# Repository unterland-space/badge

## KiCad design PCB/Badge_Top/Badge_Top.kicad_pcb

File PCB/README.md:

# Unterland Badge
The Unterland Badge is made of two PCBs, Top and Bottom.

## External Parts
- Lithium Polymer Battery with JST PH 2 Connector and Built-In Protection Circuit
  - The max. dimensions are 50mm length x 30mm width x 4mm height
  - The JST PH 2 Connector has pin 1 as positive terminal
  - This Badge does not have any protection against under- or overvoltage. Please make sure the battery has a protection circuit built-in.

- Screws
  - 3x Metal M2 5-7mm
  - 3x Nylon M2 5-7mm

## Badge Top

The Top PCB is made with ENIG finish and has 14 SK6806 RGB LEDs. It is connected to the bottom pcb via 3 of the standoffs.

## Badge Bottom

The Bottom PCB is made with HASL lead-free and has the brains of the badge.
Features:
- WCH CH32V305 Microcontroller
- TI PCM5100 DAC
- 2x USB-C (1x USB High-Speed, 1x USB Full-Speed)
- 2x 3.5mm TRS Audio Jack, for Data and Audio communication with the Fl0wer or other Badges / Equipment
- 2x Rotating Buttons for UI
- TP4054 LiPo charge controller
- Optional Micro SD-Card with SDIO
- Optional GPIOs as 2.54mm Pinheader

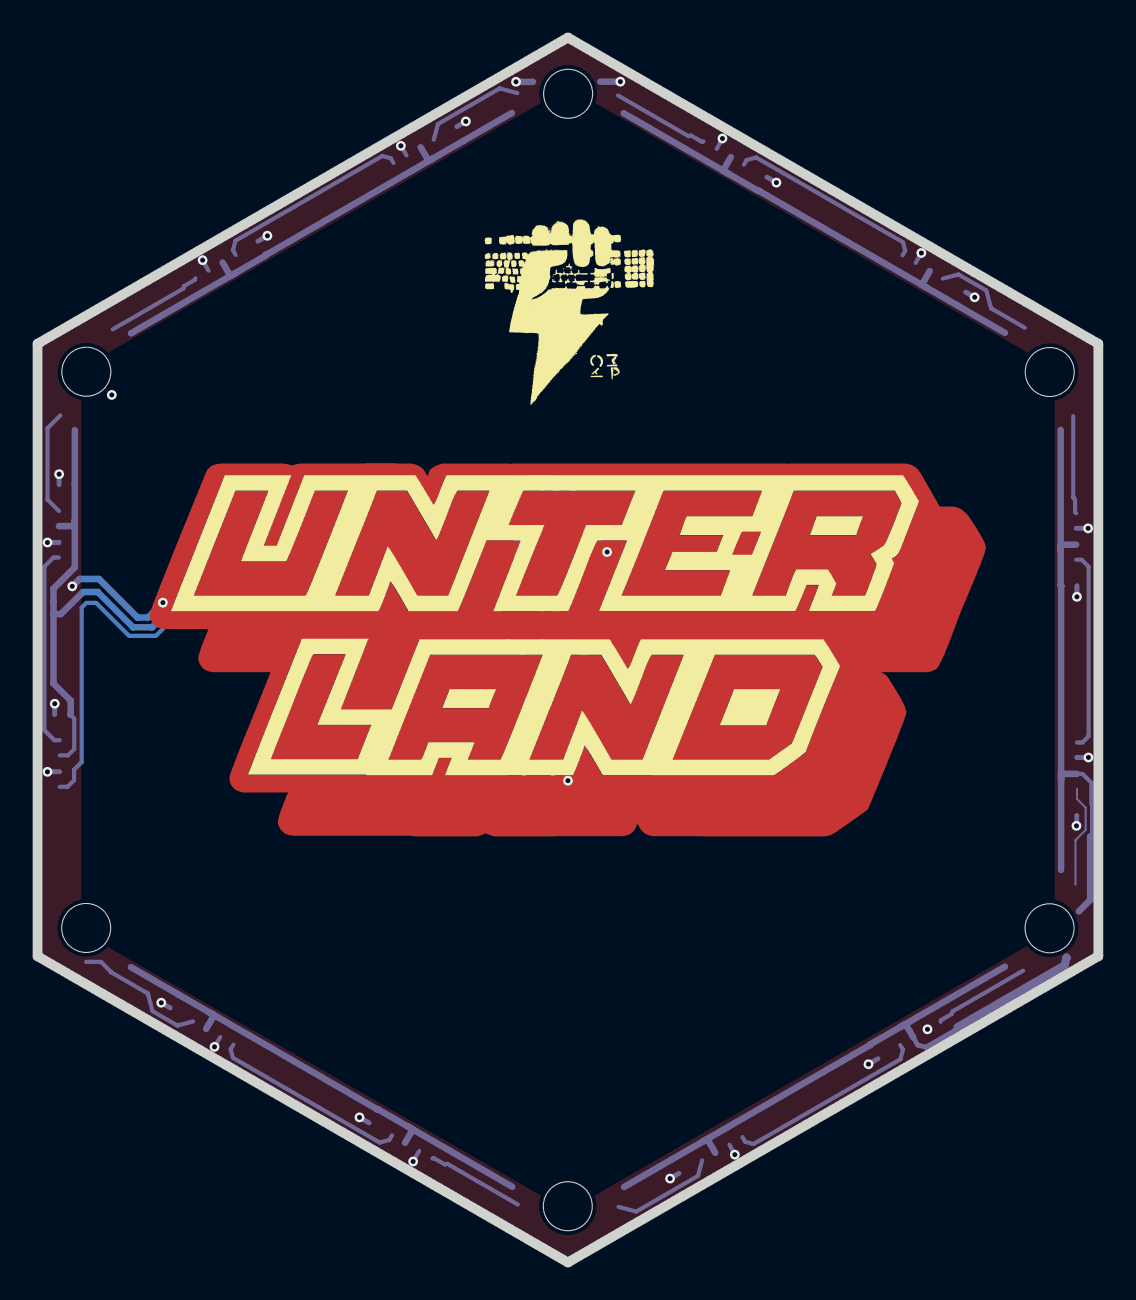
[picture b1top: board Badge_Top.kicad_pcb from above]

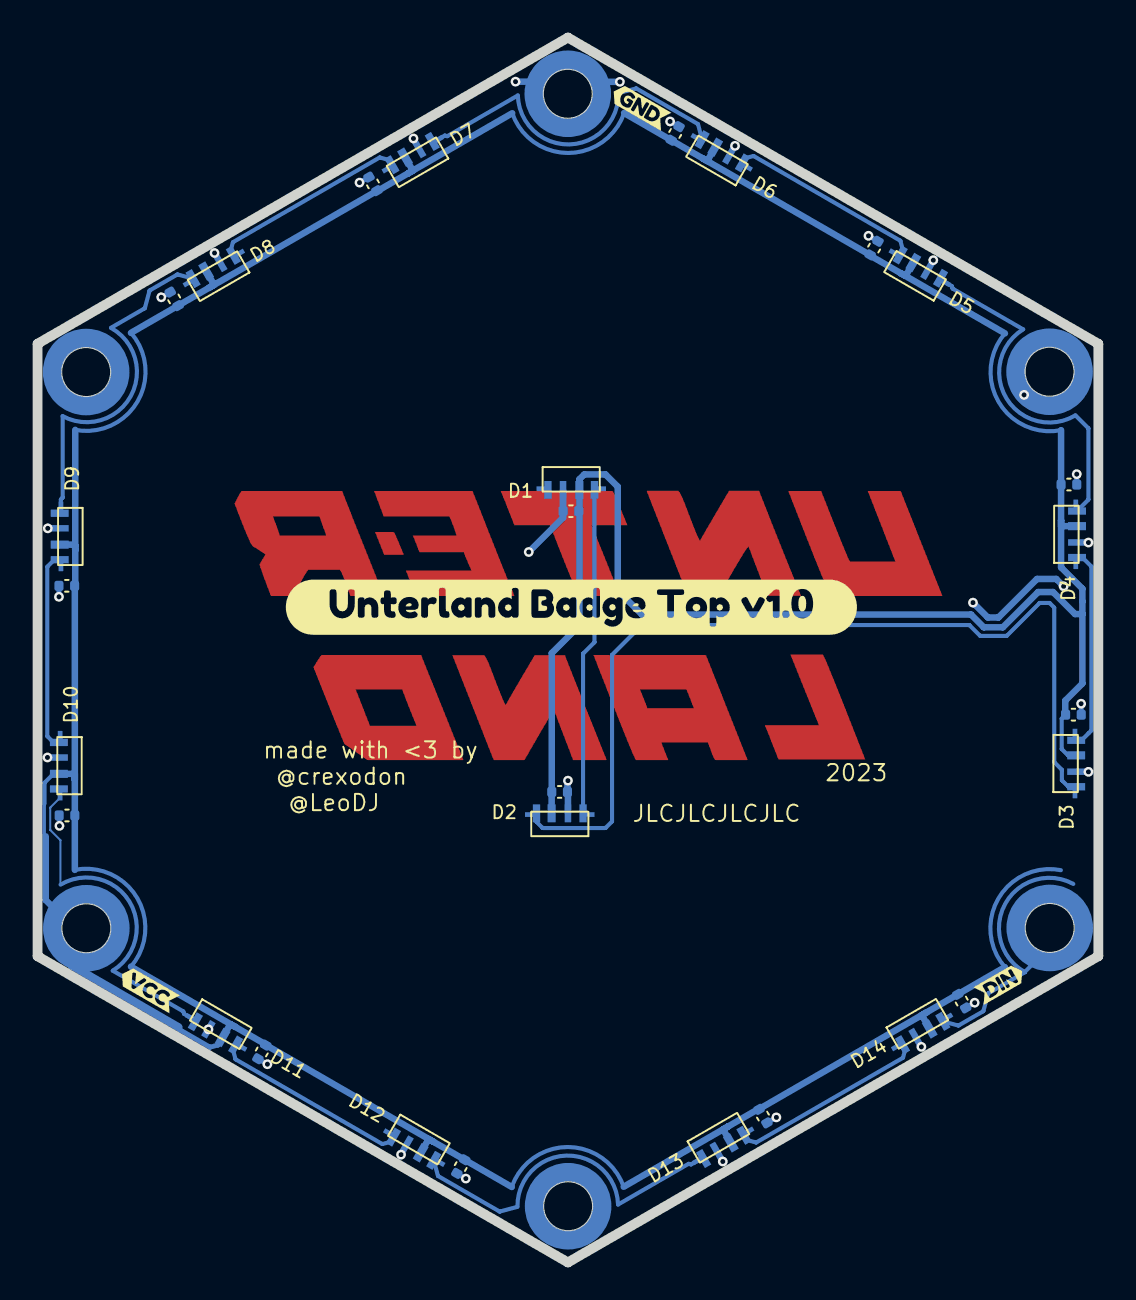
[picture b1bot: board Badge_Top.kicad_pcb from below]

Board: 2 copper layers, 65.0 x 75.0 mm, 48 parts (38 on the bottom side), 16 nets.

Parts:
1, 2, 3, 4, 5: 9966cd8a-fa79-43c1-83f9-02636052551b
6, 7, 8, 9, 10: 2488e693-1bf8-4f98-9257-4c9c6a257d6e
C1, C2, C3, C4, C5, C6, C7, C8, C9, C10, C11, C12, C13, C14: 100n; C_0402_1005Metric
D1, D2, D3, D4, D5, D6, D7, D8, D9, D10, D11, D12, D13, D14: SK6805; SK6805SIDE-G-001
J1, J2, J3, J4, J5, J6: Conn_01x01; Mounting_Wuerth_WA-SMSI-M2_H7mm_9774070243
kibuzzard-64BC5FAA: G***; kibuzzard-64BC5FAA
kibuzzard-64BC6378: G***; kibuzzard-64BC6378
kibuzzard-64BC6382: G***; kibuzzard-64BC6382
kibuzzard-64BC6413: G***; kibuzzard-64BC6413

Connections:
DIN: D14.3 (DIN), J3.1
GND: C1.2, C2.2, C3.2, C4.2, C5.2, C6.2, C7.2, C8.2, C9.2, C10.2, C11.2, C12.2, C13.2, C14.2, D1.2 (VSS), D2.2 (VSS), D3.2 (VSS), D4.2 (VSS), D5.2 (VSS), D6.2 (VSS), D7.2 (VSS), D8.2 (VSS), D9.2 (VSS), D10.2 (VSS), D11.2 (VSS), D12.2 (VSS), D13.2 (VSS), D14.2 (VSS), J1.1
unnamed: D1.3 (DIN), D2.1 (DOUT)
unnamed: D2.3 (DIN), D3.1 (DOUT)
unnamed: D3.3 (DIN), D4.1 (DOUT)
unnamed: 5.1, D4.3 (DIN), D5.1 (DOUT)
unnamed: D5.3 (DIN), D6.1 (DOUT)
unnamed: 4.1, D6.3 (DIN), D7.1 (DOUT)
unnamed: D7.3 (DIN), D8.1 (DOUT)
unnamed: 3.1, D8.3 (DIN), D9.1 (DOUT)
unnamed: 2.1, D10.3 (DIN), D11.1 (DOUT)
unnamed: D9.3 (DIN), D10.1 (DOUT)
unnamed: D11.3 (DIN), D12.1 (DOUT)
unnamed: 1.1, D12.3 (DIN), D13.1 (DOUT)
unnamed: D13.3 (DIN), D14.1 (DOUT)
VDD: 6.1, 7.1, 8.1, 9.1, 10.1, C1.1, C2.1, C3.1, C4.1, C5.1, C6.1, C7.1, C8.1, C9.1, C10.1, C11.1, C12.1, C13.1, C14.1, D1.4 (VDD), D2.4 (VDD), D3.4 (VDD), D4.4 (VDD), D5.4 (VDD), D6.4 (VDD), D7.4 (VDD), D8.4 (VDD), D9.4 (VDD), D10.4 (VDD), D11.4 (VDD), D12.4 (VDD), D13.4 (VDD), D14.4 (VDD), J5.1

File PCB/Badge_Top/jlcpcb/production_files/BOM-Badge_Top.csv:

Comment,Designator,Footprint,LCSC
100n,"C1,C10,C11,C12,C13,C14,C2,C3,C4,C5,C6,C7,C8,C9",C_0402_1005Metric,C1525
SK6805,"D1,D10,D11,D12,D13,D14,D2,D3,D4,D5,D6,D7,D8,D9",SK6805SIDE-G-001,C2909060
Conn_01x01,"J1,J2,J3,J4,J5,J6",Mounting_Wuerth_WA-SMSI-M2_H7mm_9774070243,C2916355

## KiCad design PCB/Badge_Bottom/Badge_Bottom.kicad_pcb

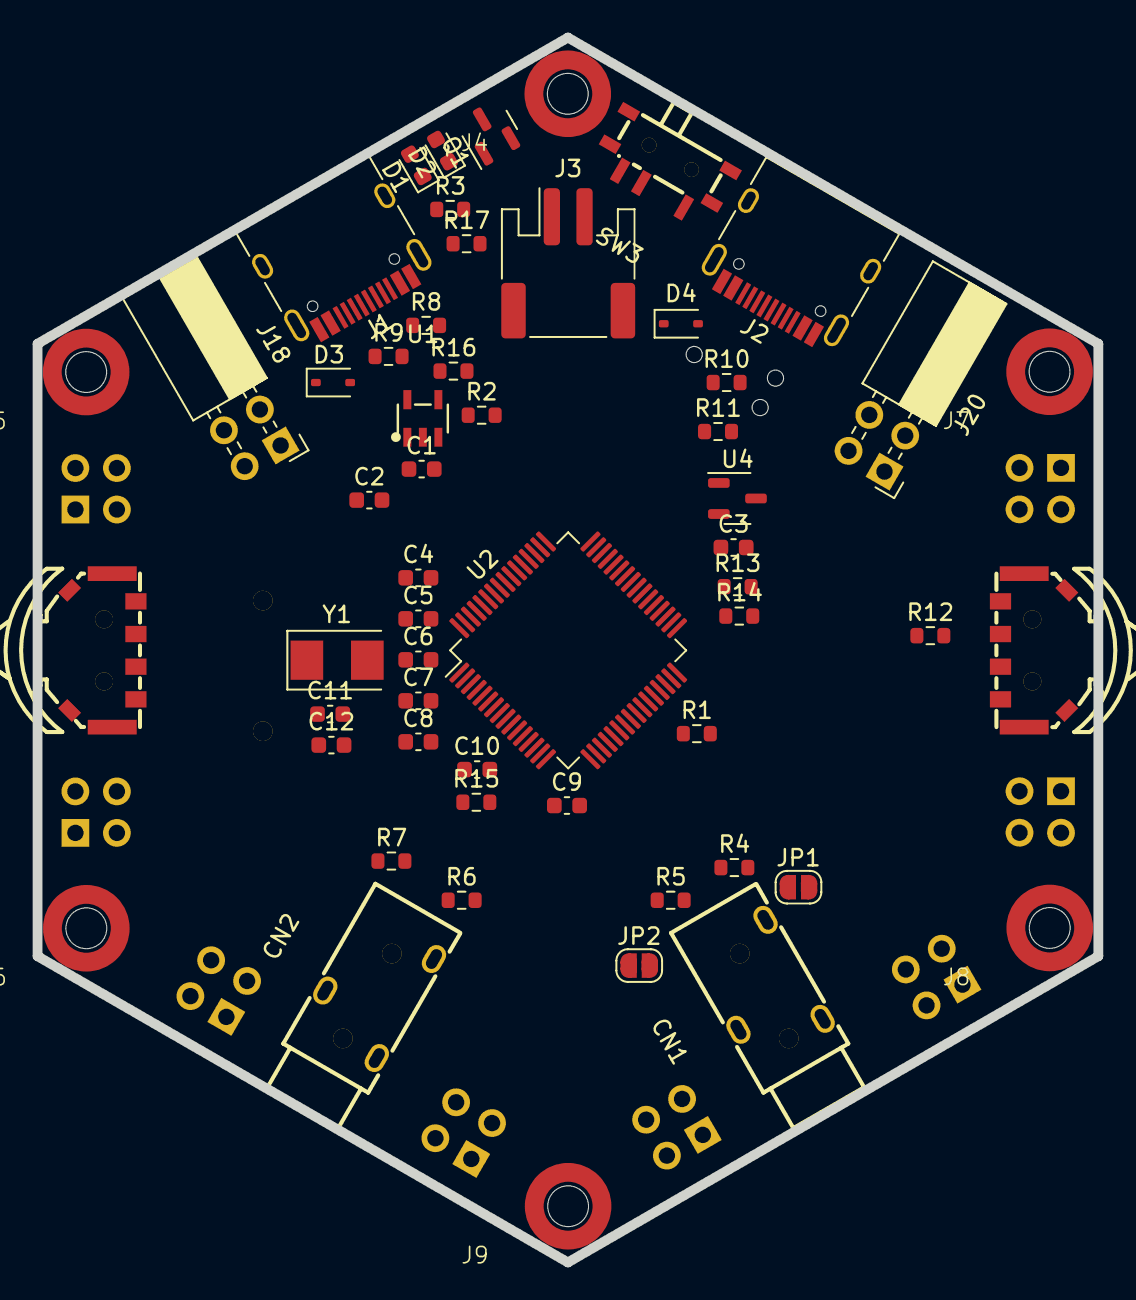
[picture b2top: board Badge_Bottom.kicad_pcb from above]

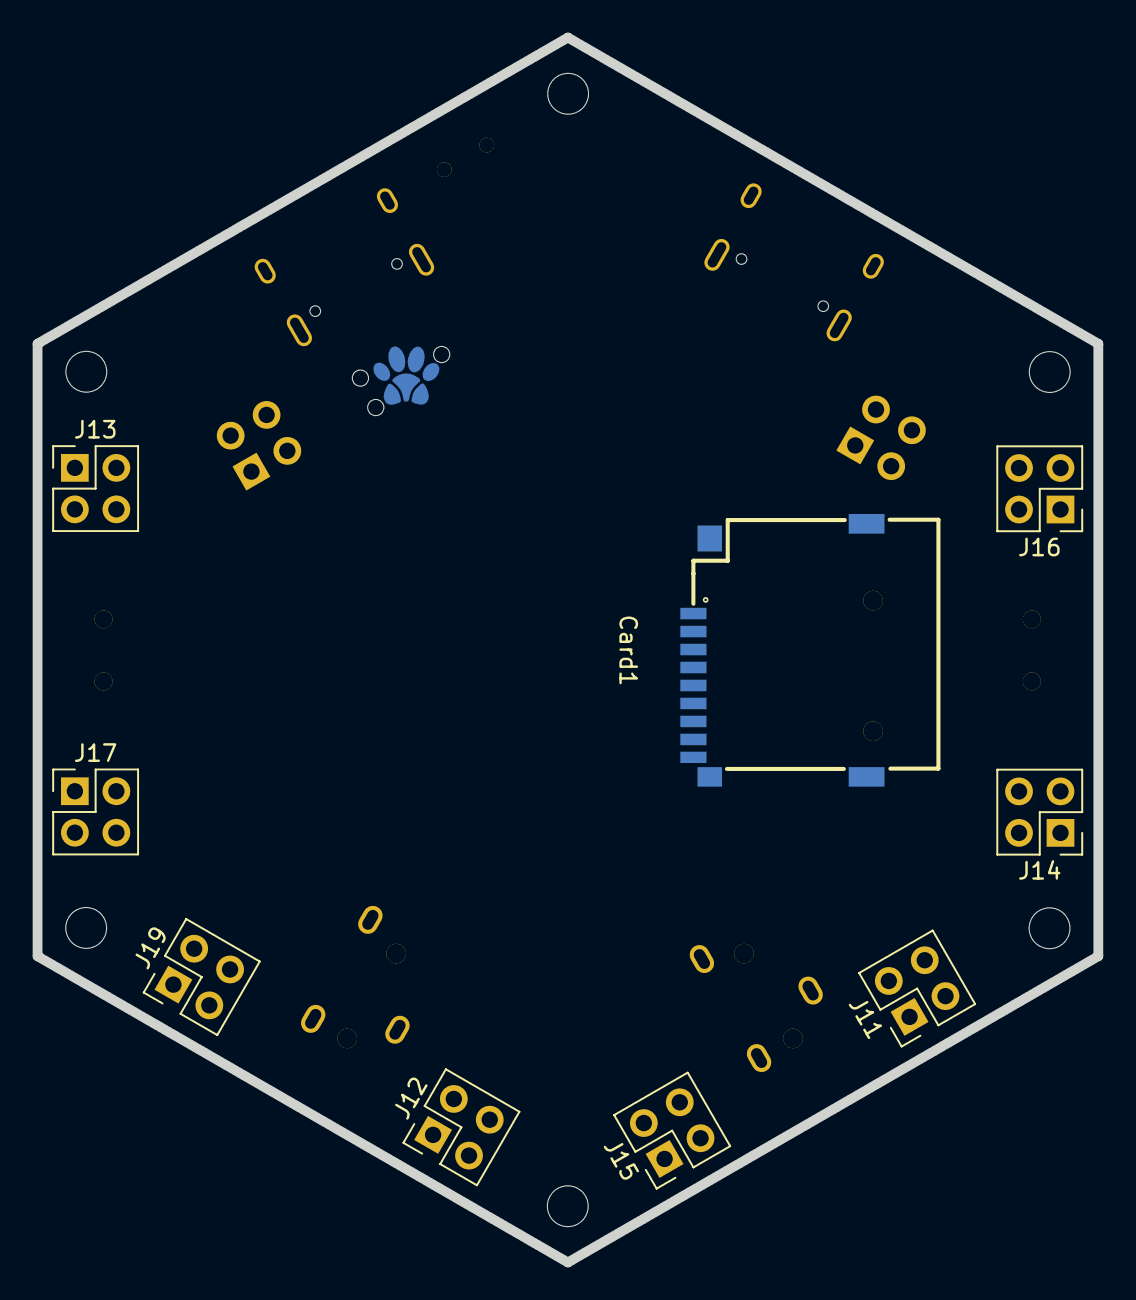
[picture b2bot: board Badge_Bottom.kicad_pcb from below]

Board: 2 copper layers, 65.0 x 75.0 mm, 66 parts (10 on the bottom side), 70 nets, no tracks yet.

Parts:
C1, C2, C3: 1u; C_0603_1608Metric
C4, C5, C6, C7, C8, C9, C10: 0.1u; C_0603_1608Metric
C11, C12: 20p; C_0603_1608Metric
CN1: JACK_IN; AUDIO-TH_HOOYA_PJ-320
CN2: JACK_OUT; AUDIO-TH_HOOYA_PJ-320
Card1: MicroSD; TF-SMD_TF-PUSH
D1: CHG; LED_0603_1608Metric
D2: USER; LED_0603_1608Metric
D3, D4: 1N5819; D_SOD-323
J1: USB_FS; USB_C_Receptacle_HRO_TYPE-C-31-M-12
J2: USB_HS; USB_C_Receptacle_HRO_TYPE-C-31-M-12
J3: BAT; JST_PH_S2B-PH-SM4-TB_1x02-1MP_P2.00mm_Horizontal
J4, J6, J8: Nylon Screw; Standoff_Pad_M2
J5, J7, J9: Metal Screw; Standoff_Pad_M2
J10: Debug; Paw-Connect_RevB_TC2030-IDC-NL_2x03_P1.27mm_Vertical
J11, J19: Power; PinHeader_2x02_P2.54mm_Vertical
J12, J13, J14, J15, J16, J17: GPIO; PinHeader_2x02_P2.54mm_Vertical
J18: SAO; PinSocket_2x02_P2.54mm_Horizontal
J20: Debug; PinSocket_2x02_P2.54mm_Horizontal
JP1, JP2: SolderJumper_2_Open; SolderJumper-2_P1.3mm_Open_RoundedPad1.0x1.5mm
Q1: AO3400A; SOT-23
R1, R12, R15, R16: 10k; R_0603_1608Metric
R2: 1.65k; R_0603_1608Metric
R3: 330; R_0603_1608Metric
R4, R5, R6, R7: 100; R_0603_1608Metric
R8, R9, R10, R11: 5k1; R_0603_1608Metric
R13, R14: 1M; R_0603_1608Metric
R17: 1k; R_0603_1608Metric
SW1, SW2: TM-2024A; SW-SMD_TM-2024A
SW3: MSK12C02-HB; SW-TH_MSK12C02-HB-1
U1: TP4054; SOT-23-5_L3.0-W1.7-P0.95-LS2.8-BL
U2: CH32V305RBT6; LQFP-64_10x10mm_P0.5mm
U4: XC6206PxxxMR; SOT-23-3
Y1: 8M; Crystal_SMD_5032-2Pin_5.0x3.2mm

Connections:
+3V3: C2.2, C4.1, C5.1, C6.2, C7.1, C8.1, Card1.4 (VDD), J10.1, J11.1, J11.2, J18.1, J19.1, R15.2, R16.1, R17.2, SW1.4, SW2.4, U2.13 (VDDA), U2.19 (VDD), U2.32 (VIO), U2.48 (VDD), U2.64 (VIO), U4.2 (VO)
+BATT: J3.1, SW3.1, U1.3 (BAT)
BOOT0: R12.2, SW1.3, U2.29 (PB10), U2.60 (BOOT0)
GND: C1.1, C2.1, C3.1, C4.2, C5.2, C6.1, C7.2, C8.2, C9.2, C10.1, C11.1, C12.1, CN1.3, CN2.3, Card1.6 (VSS), Card1.10, Card1.11, Card1.12, Card1.13, J1.A1 (GND), J1.A12 (GND), J1.B1 (GND), J1.B12 (GND), J1.S1 (SHIELD), J2.A1 (GND), J2.A12 (GND), J2.B1 (GND), J2.B12 (GND), J2.S1 (SHIELD), J3.2, J10.5, J11.3, J11.4, J18.3, J19.3, J19.4, J20.1, Q1.2 (S), R1.2, R2.2, R8.2, R9.2, R10.2, R11.2, R12.1, R14.1, SW3.4, U1.2 (GND), U2.12 (VSSA), U2.18 (VSS), U2.31 (VSS), U2.47 (VSS), U2.63 (VSS), U4.1 (GND)
NRST: C10.2, J10.3, J20.3, R15.1, U2.7 (NRST)
unnamed: CN1.2, R5.2
unnamed: CN1.4, R4.2
unnamed: CN2.2, R7.2
unnamed: CN2.4, R6.2
unnamed: D1.1 (K), R3.1
unnamed: D2.2 (A), U2.23 (PA7)
unnamed: D2.1 (K), R17.1
unnamed: D3.2 (A), J1.A4 (VBUS), J1.A9 (VBUS), J1.B4 (VBUS), J1.B9 (VBUS)
unnamed: D4.2 (A), J2.A4 (VBUS), J2.A9 (VBUS), J2.B4 (VBUS), J2.B9 (VBUS)
unnamed: J1.A5 (CC1), R8.1
unnamed: J1.B5 (CC2), R9.1
unnamed: J2.A5 (CC1), R10.1
unnamed: J2.B5 (CC2), R11.1
unnamed: J4.1, Q1.3 (D)
unnamed: R3.2, U1.1 (CHRG)
unnamed: R2.1, U1.5 (PROG)
unnamed: R1.1, U2.28 (BOOT1/PB2)
unnamed: C11.2, U2.5 (OSC_IN), Y1.2
unnamed: C12.2, U2.6 (OSC_OUT), Y1.1
PA0-GPIO: J17.1, U2.14 (WAKEUP/PA0)
PA1-ADC_IN1: C9.1, R13.1, R14.2, U2.15 (PA1)
PA2-ADC_IN2/USART2_TX: JP2.2 (B), R5.1, U2.16 (PA2)
PA3-ADC_IN_3/USART2_RX: JP1.2 (B), R4.1, U2.17 (PA3)
PA4-DAC1: R6.1, U2.20 (PA4), U2.42 (PA9)
PA6-LEDFET: Q1.1 (G), R16.2, U2.22 (PA6)
PA8-TIM1: J6.1, U2.41 (PA8)
PA10-USART1_RX: R7.1, U2.21 (PA5), U2.43 (PA10)
PA11-USBFS_DM: J1.A7 (D-), J1.B7 (D-), U2.44 (PA11)
PA12-USBFS_DP: J1.A6 (D+), J1.B6 (D+), U2.45 (PA12)
PA13-SWD: J10.2, J20.2, U2.46 (PA13)
PA14-SWCLK: J10.4, J20.4, U2.49 (PA14)
PA15-SPI1_NSS: J16.4, U2.50 (PA15)
PB0-UART4_TX: JP1.1 (A), U2.26 (PB0)
PB1-UART4_RX: JP2.1 (A), U2.27 (PB1)
PB3-SPI1_SCK: J16.1, U2.55 (PB3)
PB4-SPI1_MISO: J16.2, U2.56 (PB4)
PB5-SPI1_MOSI: J16.3, U2.57 (PB5)
PB6-USBHS_DM: J2.A7 (D-), J2.B7 (D-), U2.58 (PB6)
PB7-USBHS_DP: J2.A6 (D+), J2.B6 (D+), U2.59 (PB7)
PB8-I2C_SCL: J17.4, J18.4, U2.61 (PB8)
PB9-I2C_SDA: J17.2, J18.2, U2.62 (PB9)
PB11-BTNR_UP: SW1.1, U2.30 (PB11)
PB12-BNTR_DOWN: SW1.2, U2.33 (PB12)
PB13-BTNL-BTN: SW2.3, U2.34 (PB13)
PB14-BTNL_UP: SW2.2, U2.35 (PB14)
PB15-BTNL_DOWN: SW2.1, U2.36 (PB15)
PC0-GPIO: J12.1, U2.8 (PC0)
PC1-GPIO: J12.2, U2.9 (PC1)
PC2-GPIO: J12.3, U2.10 (PC2)
PC3-GPIO: J12.4, U2.11 (PC3)
PC4-GPIO: J13.1, U2.24 (PC4)
PC5-GPIO: J13.2, U2.25 (PC5)
PC6-GPIO: J13.3, U2.37 (PC6)
PC7-GPIO: J13.4, U2.38 (PC7)
PC8-SDIO_D0: Card1.7 (DAT0), J14.1, U2.39 (PC8)
PC9-SDIO_D1: Card1.8 (DAT1), J14.2, U2.40 (PC9)
PC10-SDIO_D2: Card1.1 (DAT2), J14.3, U2.51 (PC10)
PC11-SDIO_D3: Card1.2 (CD/DAT3), J14.4, U2.52 (PC11)
PC12-SDIO_CLK: Card1.5 (CLX), J15.1, U2.53 (PC12)
PC13-SDIO_CD: J15.2, U2.2 (PC13/TAMPER-RTC)
PC14-GPIO: J15.3, U2.3 (PC14/OSC32_IN)
PC15-GPIO: J15.4, U2.4 (PC15/OSC32_OUT)
PD2-SDIO_CMD: Card1.3 (CMD), J17.3, U2.54 (PD2)
VBUS: C1.2, D1.2 (A), D3.1 (K), D4.1 (K), U1.4 (VCC)
VDD: C3.2, J8.1, J19.2, R13.2, SW3.2, U4.3 (VI)

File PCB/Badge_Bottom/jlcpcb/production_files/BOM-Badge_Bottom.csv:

Comment,Designator,Footprint,LCSC
8M,Y1,Crystal_SMD_5032-2Pin_5.0x3.2mm,C115962
0.1u,"C10,C4,C5,C6,C7,C8,C9",C_0603_1608Metric,C14663
1u,"C1,C2,C3",C_0603_1608Metric,C15849
20p,"C11,C12",C_0603_1608Metric,C1648
USB_FS,"J1,J2",USB_C_Receptacle_HRO_TYPE-C-31-M-12,C165948
1N5819,"D3,D4",D_SOD-323,C191023
AO3400A,Q1,SOT-23,C20917
1k,R17,R_0603_1608Metric,C21190
CHG,D1,LED_0603_1608Metric,C2286
1M,"R13,R14",R_0603_1608Metric,C22935
330,R3,R_0603_1608Metric,C23138
5k1,"R10,R11,R8,R9",R_0603_1608Metric,C23186
10k,"R1,R12,R15,R16,R4,R5,R6,R7",R_0603_1608Metric,C25804
Nylon Screw,"J4,J5,J6,J7,J8,J9",Standoff_Pad_M2,C2928186
1.65k,R2,R_0603_1608Metric,C2930051
JACK_IN,"CN1,CN2",AUDIO-TH_HOOYA_PJ-320,C2939180
BAT,J3,JST_PH_S2B-PH-SM4-TB_1x02-1MP_P2.00mm_Horizontal,C3029440
TP4054,U1,SOT-23-5_L3.0-W1.7-P0.95-LS2.8-BL,C32574
MSK12C02-HB,SW3,SW-TH_MSK12C02-HB-1,C431541
CH32V305RBT6,U2,LQFP-64_10x10mm_P0.5mm,C5187529
XC6206PxxxMR,U4,SOT-23-3,C5446
TM-2024A,"SW1,SW2",SW-SMD_TM-2024A,C561480
USER,D2,LED_0603_1608Metric,C72043
SolderJumper_2_Open,JP2,SolderJumper-2_P1.3mm_Open_RoundedPad1.0x1.5mm,
SolderJumper_2_Open,JP1,SolderJumper-2_P1.3mm_Open_RoundedPad1.0x1.5mm,
Debug,J10,Paw-Connect_RevB_TC2030-IDC-NL_2x03_P1.27mm_Vertical,

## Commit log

2023-07-17 Init
2023-07-18 added symbols and footprints
2023-07-18 Added todo for bottom badge
2023-07-18 do layout of top PCB, generated preliminary gerbers
2023-07-21 Added pcb outline from Badge_Top, added todos in pcb file
2023-07-22 Added new page for IO, added new components, added JLC parts, fixed PCB standoffs to be pads and modified concept of PCB (dual usbc)
2023-07-22 better silkscreen, remove DOUT
2023-07-23 finished schematic and added jlc parts
2023-07-23 saved files
2023-07-29 finised pcb layout
2023-07-29 added all missing jlcpcb numbers, order ready
2023-07-29 Added docs and readme, ordered PCBs at JLC
2023-08-19 initial firmware
2023-08-19 copy LED "library" from LEDCollar
2023-08-19 modify LED "library" for CH32V3xx
2023-08-19 add basic FW readme
